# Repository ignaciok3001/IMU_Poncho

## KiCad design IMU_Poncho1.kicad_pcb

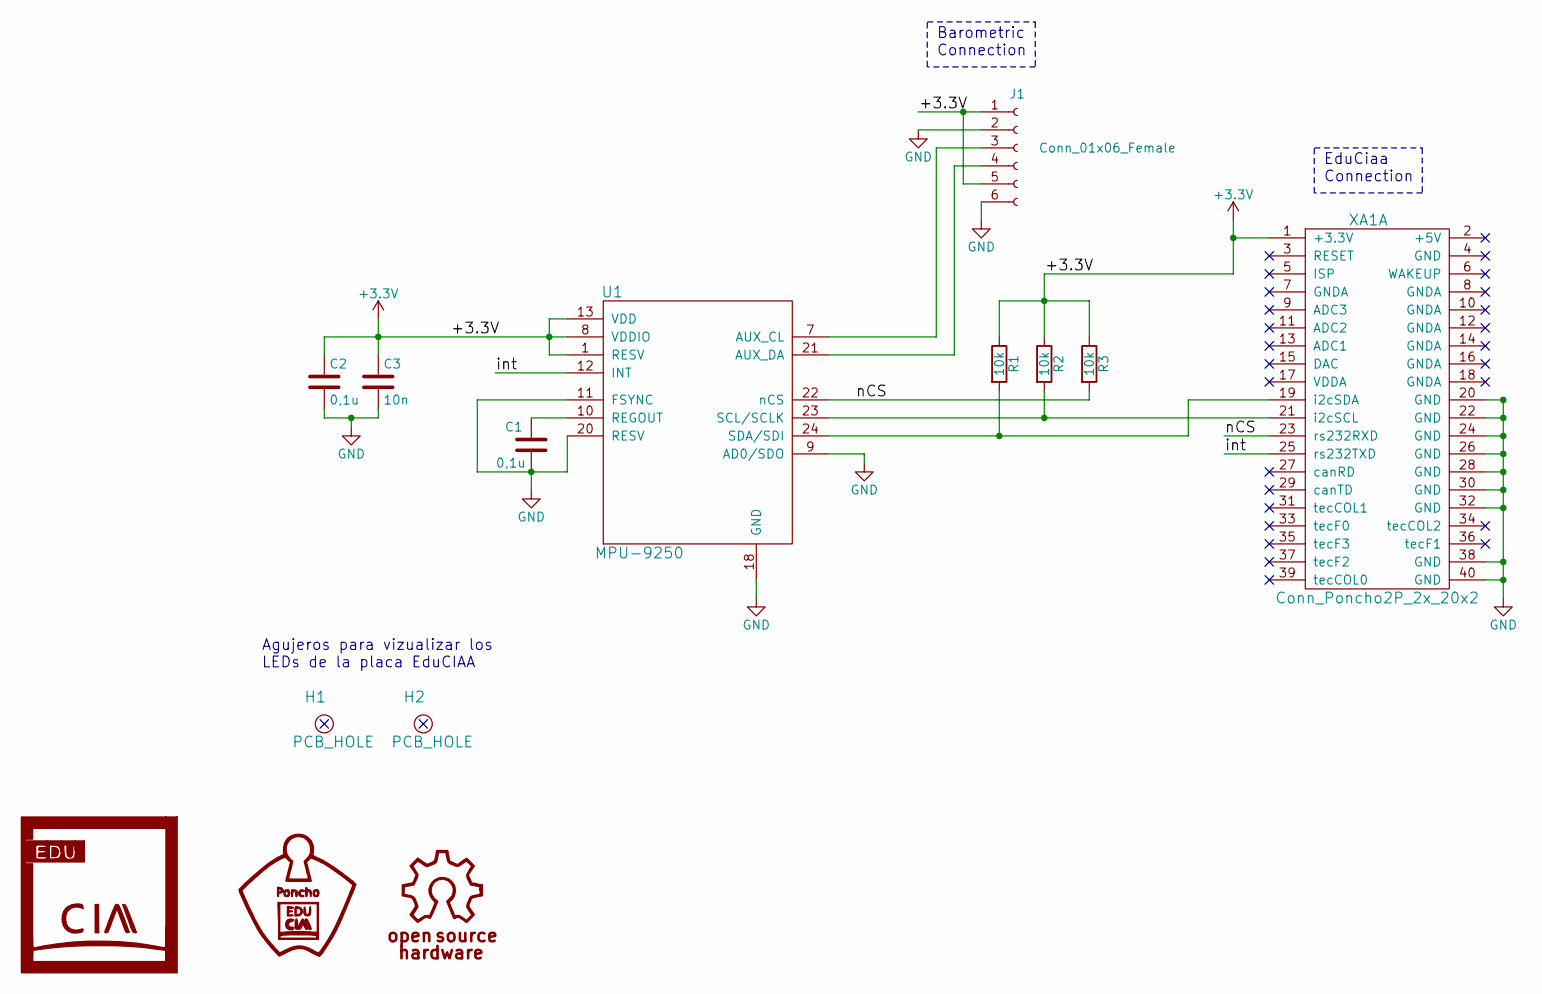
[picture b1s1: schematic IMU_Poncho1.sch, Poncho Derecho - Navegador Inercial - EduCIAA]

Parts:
C1: 0,1u; C_0805_HandSoldering; Digikey# 478-1395-2-ND
C2: 0,1u; C_0805_HandSoldering; Digikey# 08055C104KAT2A
C3: 10n; C_0805_HandSoldering; Digikey# 311-1136-1-ND
H1, H2: PCB_HOLE; Led_Hole
J1: Conn_01x06_Female; bornier6; Digikey# 929974E-01-06-ND
R1: 10k; R_0805_HandSoldering; Digikey# CC0805KRX7R9BB103
R2, R3: 10k; R_0805_HandSoldering; Digikey# CR0805-JW-103GLF-ND
U1: MPU-9250; QFN-24_3x3mm_Pitch0.4mm_NoMask; Digikey# 1428-1019-1-ND
XA1: Conn_Poncho2P_2x_20x2; Conn_Poncho_Derecha; Digikey 952-1897-ND

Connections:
+3V3: C2.1, C3.1, J1.1, J1.5, R1.1, R2.1, R3.1, U1.1 (RESV), U1.8 (VDDIO), U1.13 (VDD), XA1.1 (+3.3V)
/int: U1.12 (INT), XA1.25 (rs232TXD)
/nCS: R3.2, U1.22 (nCS), XA1.23 (rs232RXD)
GND: C1.2, C2.2, C3.2, J1.2, J1.6, U1.9 (AD0/SDO), U1.11 (FSYNC), U1.18 (GND), U1.20 (RESV), XA1.20 (GND), XA1.22 (GND), XA1.24 (GND), XA1.26 (GND), XA1.28 (GND), XA1.30 (GND), XA1.32 (GND), XA1.38 (GND), XA1.40 (GND)
unnamed: C1.1, U1.10 (REGOUT)
unnamed: J1.3, U1.7 (AUX_CL)
unnamed: J1.4, U1.21 (AUX_DA)
unnamed: R1.2, U1.24 (SDA/SDI), XA1.19 (i2cSDA)
unnamed: R2.2, U1.23 (SCL/SCLK), XA1.21 (i2cSCL)

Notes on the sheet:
EduCiaa Connection
Barometric Connection
Agujeros para vizualizar los LEDs de la placa EduCIAA

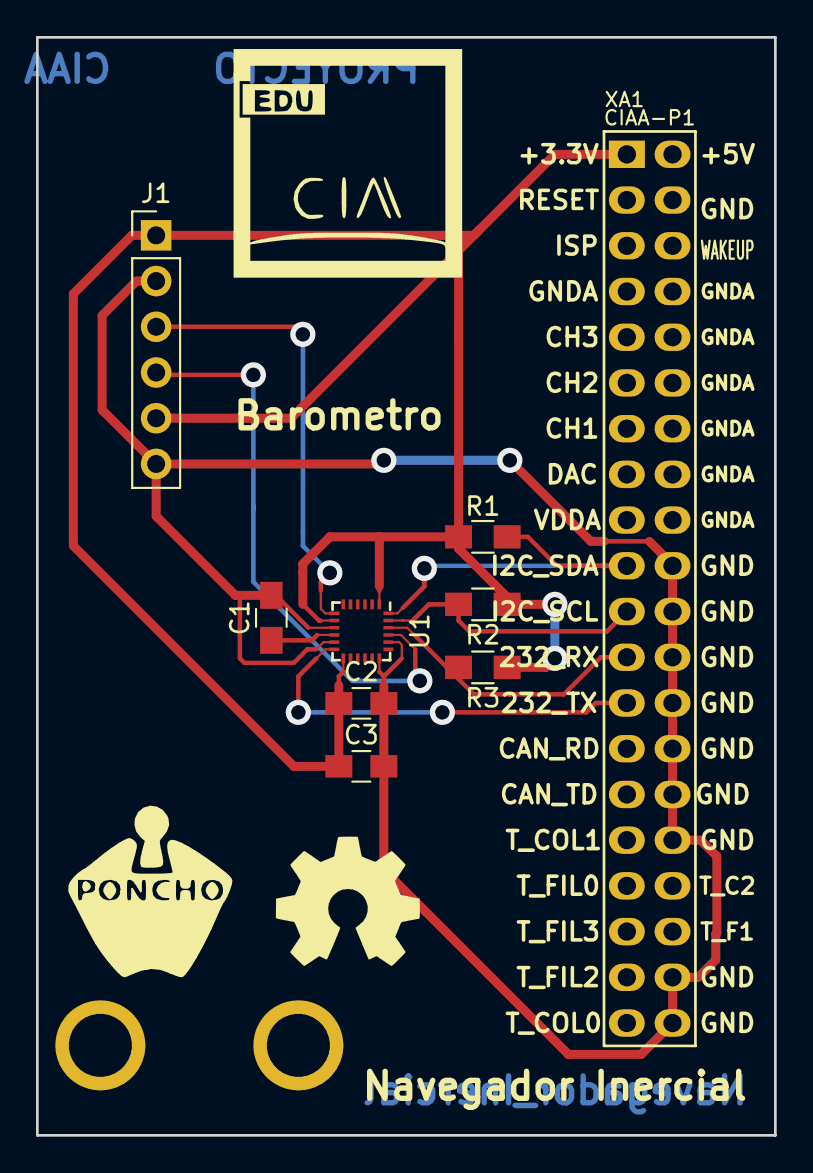
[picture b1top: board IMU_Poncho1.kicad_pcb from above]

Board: 2 copper layers, 41.0 x 61.0 mm, 14 parts (0 on the bottom side), 9 nets.

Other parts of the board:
G1: LOGO; Logo_Poncho
G2: Logo_OSHWA
G3: Logo_EDU-CIAA

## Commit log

2017-10-02 subiendo preliminares
2017-10-30 Subiendo
    Esquematico y primeros archivos subidos
2017-10-31 Corrigiendo esquematico + datasheets
    Detalles de lineas y pines para que no se crucen, +pwr
2017-11-23 El pcb
2017-11-23 Correccion del conector del barometro y se lo coloca separado del IMU. Dibujo 3D
2017-11-24 Corrigiendo seguimiento de archivos, borrando del grupo
2017-11-24 Reconstruyendo archivos
    Colocando los archivos que se abrieron a otra rama
